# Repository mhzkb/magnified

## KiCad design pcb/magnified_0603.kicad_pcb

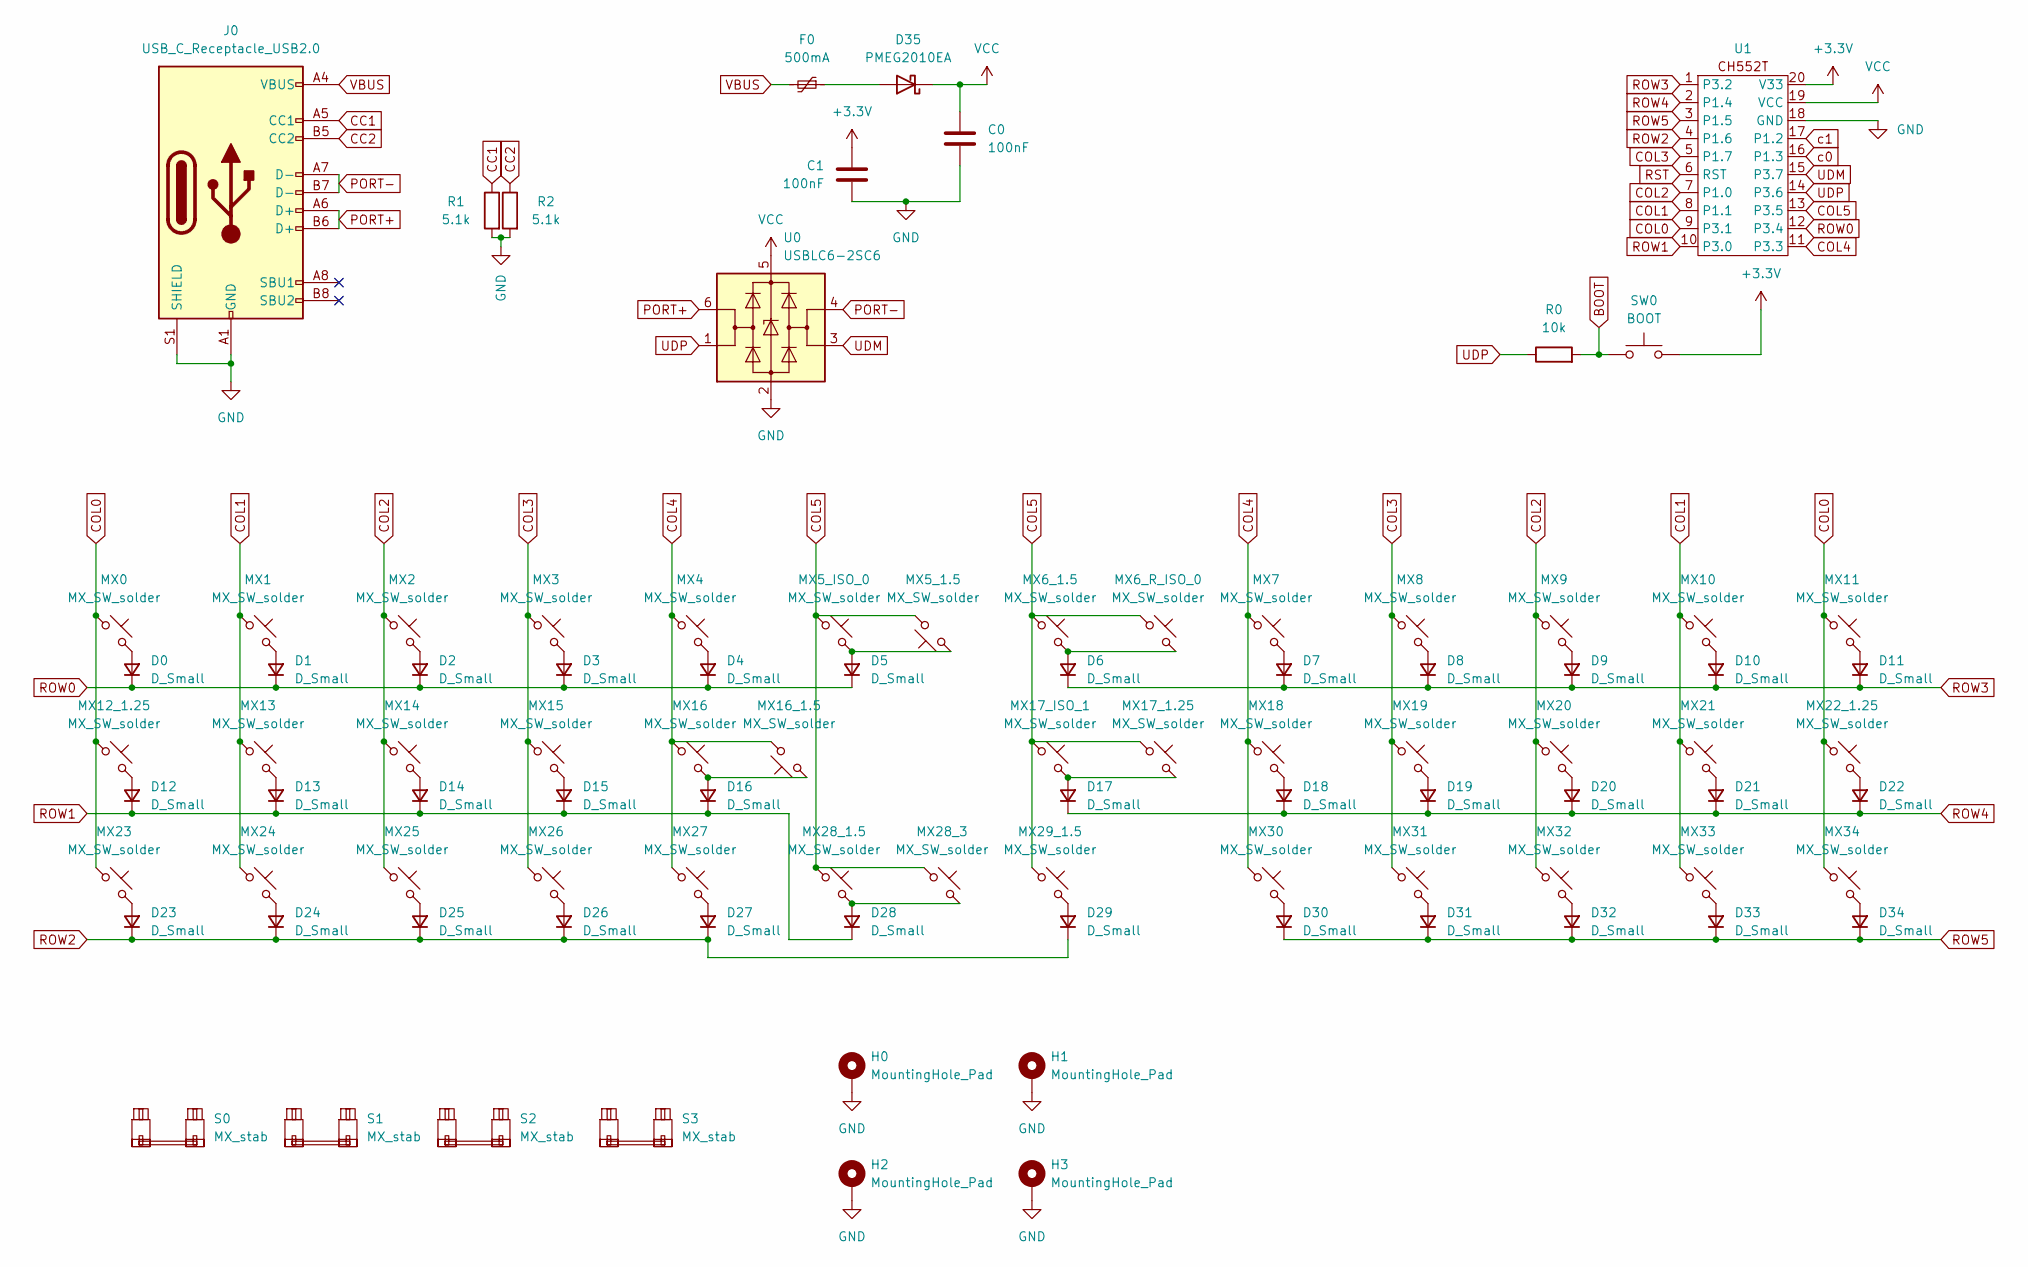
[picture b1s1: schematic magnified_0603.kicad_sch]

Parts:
C0, C1: 100nF; C_0603_1608Metric; LCSC C1525
D0, D1, D2, D3, D4, D5, D6, D7, D8, D9, D10, D11, D12, D13, D14, D15, D16, D17, D18, D19, D20, D21, D22, D23, D24, D25, D26, D27, D28, D29, D30, D31, D32, D33, D34: D_Small; D_SOD-123
D35: PMEG2010EA; D_SOD-323_HandSoldering; LCSC C2837790
F0: 500mA; Fuse_0603_1608Metric; LCSC C210357
H0, H1, H2, H3: MountingHole_Pad; MountingHole_2.2mm_M2_Pad_Via
J0: USB_C_Receptacle_USB2.0; USB_C_Receptacle_HRO_TYPE-C-31-M-12; JLCPCB_CORRECTION 0; -1.35; 0
MX0, MX1, MX2, MX3, MX4, MX5_ISO_0, MX6_R_ISO_0, MX7, MX8, MX9, MX10, MX11, MX13, MX14, MX15, MX16, MX17_ISO_1, MX18, MX19, MX20, MX21, MX23, MX24, MX25, MX26, MX27, MX28_3, MX30, MX31, MX32, MX33, MX34: MX_SW_solder; SW_MX_1u
MX5_1.5, MX6_1.5, MX16_1.5, MX28_1.5, MX29_1.5: MX_SW_solder; SW_MX_1.5u
MX12_1.25, MX17_1.25, MX22_1.25: MX_SW_solder; SW_MX_1.25u
R0: 10k; R_0603_1608Metric; LCSC C25744
R1, R2: 5.1k; R_0603_1608Metric; LCSC C25905
S0, S1, S3: MX_stab; STAB_MX_P_ISO
S2: MX_stab; STAB_MX_P_3u
SW0: BOOT; SW_Push_SPST_NO_Alps_SKRK; LCSC C115357
U0: USBLC6-2SC6; SOT-23-6; JLCPCB_CORRECTION 0; 0; 270
U1: TSSOP-20_4.4x6.5mm_P0.65mm; JLCPCB_CORRECTION 0; 0; 270

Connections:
+3.3V: C1.1, SW0.2, U1.20 (V33)
BOOT: R0.2, SW0.1
CC1: J0.A5 (CC1), R1.1
CC2: J0.B5 (CC2), R2.1
COL0: MX0.1, MX11.1, MX12_1.25.1, MX22_1.25.1, MX23.1, MX34.1, U1.9 (P3.1)
COL1: MX1.1, MX10.1, MX13.1, MX21.1, MX24.1, MX33.1, U1.8 (P1.1)
COL2: MX2.1, MX9.1, MX14.1, MX20.1, MX25.1, MX32.1, U1.7 (P1.0)
COL3: MX3.1, MX8.1, MX15.1, MX19.1, MX26.1, MX31.1, U1.5 (P1.7)
COL4: MX4.1, MX7.1, MX16.1, MX16_1.5.2, MX18.1, MX27.1, MX30.1, U1.11 (P3.3)
COL5: MX5_1.5.2, MX5_ISO_0.1, MX6_1.5.1, MX6_R_ISO_0.1, MX17_1.25.1, MX17_ISO_1.1, MX28_1.5.1, MX28_3.1, MX29_1.5.1, U1.13 (P3.5)
GND: C0.2, C1.2, H0.1, H1.1, H2.1, H3.1, J0.A1 (GND), J0.A12 (GND), J0.B1 (GND), J0.B12 (GND), J0.S1 (SHIELD), R1.2, R2.2, U0.2 (GND), U1.18 (GND)
unnamed: D0.2 (A), MX0.2
unnamed: D1.2 (A), MX1.2
unnamed: D2.2 (A), MX2.2
unnamed: D3.2 (A), MX3.2
unnamed: D4.2 (A), MX4.2
unnamed: D5.2 (A), MX5_1.5.1, MX5_ISO_0.2
unnamed: D6.2 (A), MX6_1.5.2, MX6_R_ISO_0.2
unnamed: D7.2 (A), MX7.2
unnamed: D8.2 (A), MX8.2
unnamed: D9.2 (A), MX9.2
unnamed: D10.2 (A), MX10.2
unnamed: D11.2 (A), MX11.2
unnamed: D12.2 (A), MX12_1.25.2
unnamed: D13.2 (A), MX13.2
unnamed: D14.2 (A), MX14.2
unnamed: D15.2 (A), MX15.2
unnamed: D16.2 (A), MX16.2, MX16_1.5.1
unnamed: D17.2 (A), MX17_1.25.2, MX17_ISO_1.2
unnamed: D18.2 (A), MX18.2
unnamed: D19.2 (A), MX19.2
unnamed: D20.2 (A), MX20.2
unnamed: D21.2 (A), MX21.2
unnamed: D22.2 (A), MX22_1.25.2
unnamed: D23.2 (A), MX23.2
unnamed: D24.2 (A), MX24.2
unnamed: D25.2 (A), MX25.2
unnamed: D26.2 (A), MX26.2
unnamed: D27.2 (A), MX27.2
unnamed: D28.2 (A), MX28_1.5.2, MX28_3.2
unnamed: D29.2 (A), MX29_1.5.2
unnamed: D30.2 (A), MX30.2
unnamed: D31.2 (A), MX31.2
unnamed: D32.2 (A), MX32.2
unnamed: D33.2 (A), MX33.2
unnamed: D34.2 (A), MX34.2
unnamed: D35.2 (A), F0.1
PORT+: J0.A6 (D+), J0.B6 (D+), U0.6 (I/O1)
PORT-: J0.A7 (D-), J0.B7 (D-), U0.4 (I/O2)
ROW0: D0.1 (K), D1.1 (K), D2.1 (K), D3.1 (K), D4.1 (K), D5.1 (K), U1.12 (P3.4)
ROW1: D12.1 (K), D13.1 (K), D14.1 (K), D15.1 (K), D16.1 (K), D28.1 (K), U1.10 (P3.0)
ROW2: D23.1 (K), D24.1 (K), D25.1 (K), D26.1 (K), D27.1 (K), D29.1 (K), U1.4 (P1.6)
ROW3: D6.1 (K), D7.1 (K), D8.1 (K), D9.1 (K), D10.1 (K), D11.1 (K), U1.1 (P3.2)
ROW4: D17.1 (K), D18.1 (K), D19.1 (K), D20.1 (K), D21.1 (K), D22.1 (K), U1.2 (P1.4)
ROW5: D30.1 (K), D31.1 (K), D32.1 (K), D33.1 (K), D34.1 (K), U1.3 (P1.5)
RST: U1.6 (RST)
UDM: U0.3 (I/O2), U1.15 (P3.7)
UDP: R0.1, U0.1 (I/O1), U1.14 (P3.6)
VBUS: F0.2, J0.A4 (VBUS), J0.A9 (VBUS), J0.B4 (VBUS), J0.B9 (VBUS)
VCC: C0.1, D35.1 (K), U0.5 (VBUS), U1.19 (VCC)
c0: U1.16 (P1.3)
c1: U1.17 (P1.2)

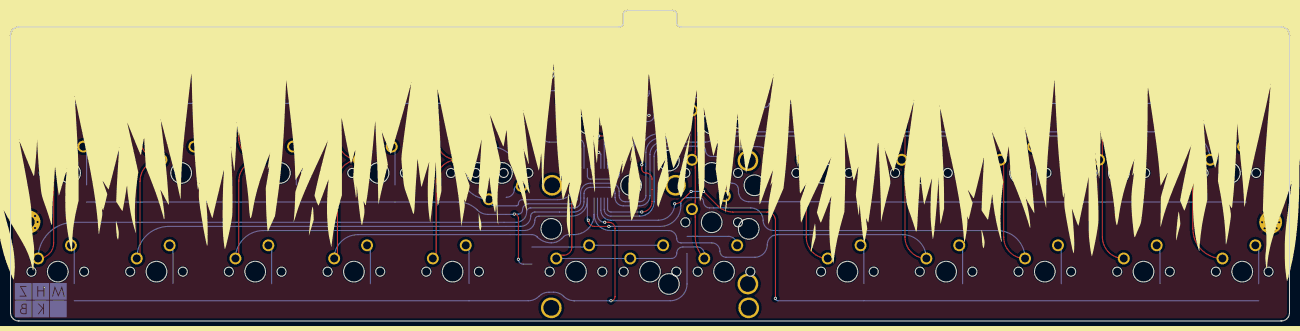
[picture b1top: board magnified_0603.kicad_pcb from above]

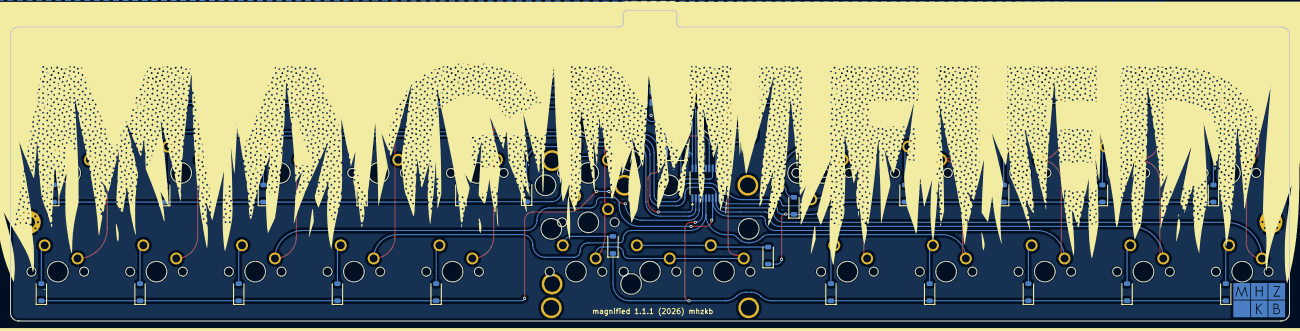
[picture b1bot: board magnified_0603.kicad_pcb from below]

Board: 2 copper layers, 246.9 x 59.9 mm, 94 parts (46 on the bottom side), 59 nets.

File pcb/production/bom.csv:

Designator,Footprint,Quantity,Value,LCSC Part #
"C0, C1",0603,2,100nF,C14663
"D0, D1, D10, D11, D12, D13, D14, D15, D16, D17, D18, D19, D2, D20, D21, D22, D23, D24, D25, D26, D27, D28, D29, D3, D30, D31, D32, D33, D34, D4, D5, D6, D7, D8, D9",D_SOD-123,35,D_Small,C81598
D35,D_SOD-323_HandSoldering,1,PMEG2010EA,C2837790
F0,0603,1,500mA,C210357
J0,USB_C_Receptacle_HRO_TYPE-C-31-M-12,1,USB_C_Receptacle_USB2.0,C2765186
R0,0603,1,10k,C25804
"R1, R2",0603,2,5.1k,C23186
SW0,SW_Push_SPST_NO_Alps_SKRK,1,BOOT,C115357
U0,SOT-23-6,1,USBLC6-2SC6,C2687116
U1,TSSOP-20_4.4x6.5mm_P0.65mm,1,~,C111367

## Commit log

2025-08-28 Added readme
2025-08-28 Added license
2026-01-21 Updated pcb silkscreen
2026-01-21 Updated bom and folder structure
2026-01-21 Added gitignore
2026-01-21 Added case and plate files
